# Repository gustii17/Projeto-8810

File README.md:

# Projeto 8810
`Projeto 8810 - Módulo Didático de Eletrônica Digital`

<h1 align="center">
  
</h1>

## Sumário 📋
 - [Objetivo](#objective)
 - [Motivação](#motivation)
 - [Projeto](#project)
 - [Arquivos](#files)
 - [Licença](#license)

## Objetivo 🎯
Desenvolver um módulo didático próprio e de baixo custo, capaz de reproduzir as principais funcionalidades do Datapool 8810, incluindo chaves, indicadores LED, protoboard, gerador de clock, ponta de prova e fontes de alimentação.

## Motivação 🚀
A disciplina de Eletrônica Digital é um componente fundamental na formação dos estudantes dos cursos de Engenharia que dependam de eletrônica. As atividades práticas na UFC (Universidade Federal do Ceará) são realizadas com o auxílio do módulo didático Datapool 8810, utilizado para a aplicação dos conceitos estudados em sala de aula. Entretanto, parte desses equipamentos apresenta desgaste e falhas de funcionamento, dificultando a realização dos experimentos. Além disso, os custos de manutenção ou substituição são elevados, evidenciando a necessidade de uma alternativa de baixo custo e de fácil manutenção.

## Projeto 🛠️
O projeto está dividido em basicamente 3 subprojetos, os quais são:
 - A PCB da Placa de Cima, resposável pela lógica e funcionamento geral do módulo, junto com o código do microcontrolador. _[Em Breve](./) mais informações_
 - A PCB da Placa de Baixo, resposável pelo fornecimento de eneriga. _[Clique Aqui](/docs/POWER-BOARD.md) para mais informações_
 - O Modelo 3D do módulo. _[Em Breve](./) mais informações_

## Arquivos 📂

```txt
.
|-- docs/       Documentação e Datasheets
|-- firmware/   Código do microcontrolador
|-- cad/        Modelo 3D
|-- schematics/ Esquemáticos, PCBs e simulações
|-- licenses/   Licenças do projeto
|-- assets/     Imagens
|-- README.md   Este Arquivo
```

## Licença 📝
O Projeto está licenciado sobre algumas licenças da seguinte forma:
 - Todos os arquivos dentro de [cad/](/cad) estão licenciadas sobre a licença [CC By 4.0](/licenses/CC-BY-4.0.txt).
 - Todos os arquivos dentro de [schematics/power-board/](/schematics/power-board) estão licenciadas sobre a licença [CERN OHL P](/licenses/CERN-OHL-P.txt).
 - Todos os arquivos dentro de [firmware/](/firmware) estão licenciados sobre a licença [...]()
 - Todos os arquivos dentro de [schematics/logic-board/](/schematics/logic-board) estão licenciadas sobre a licença [...]()
 - Todos os demais arquivos estão sobre a licença [CC0](/licenses/CC0.txt).

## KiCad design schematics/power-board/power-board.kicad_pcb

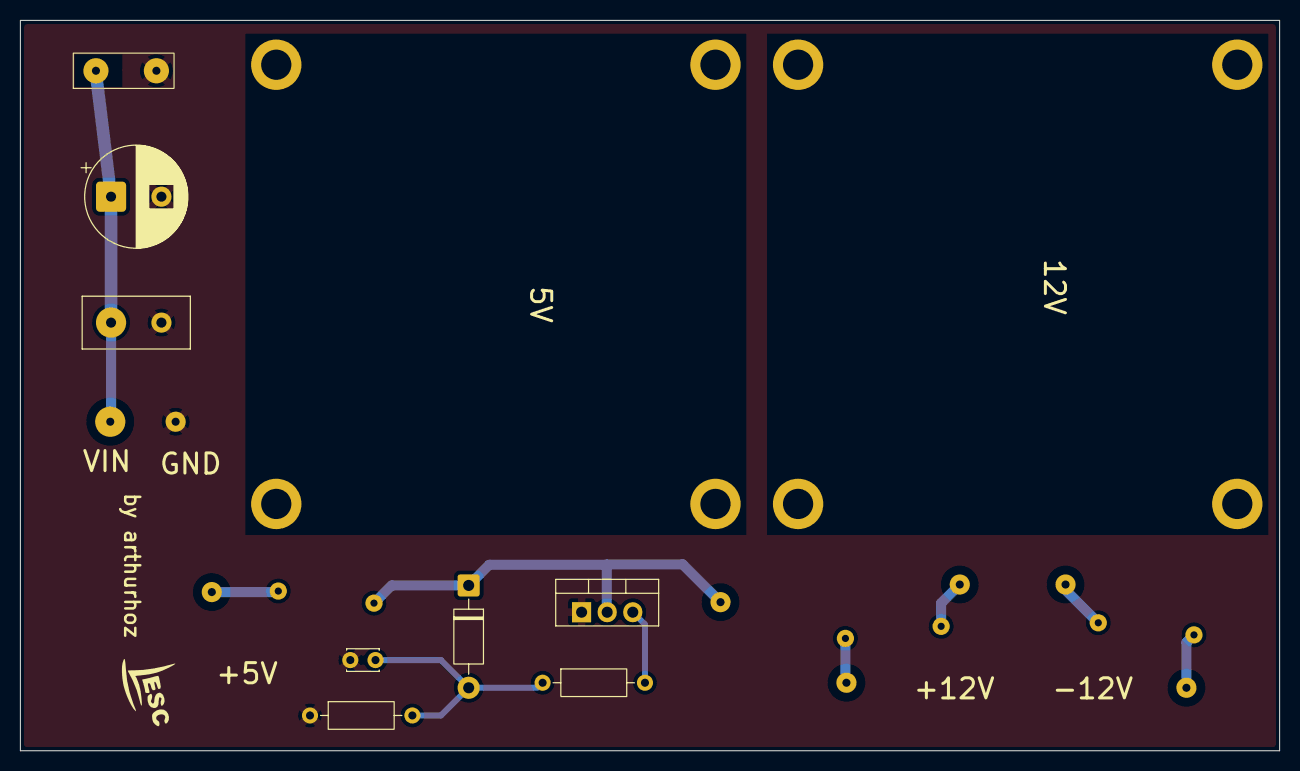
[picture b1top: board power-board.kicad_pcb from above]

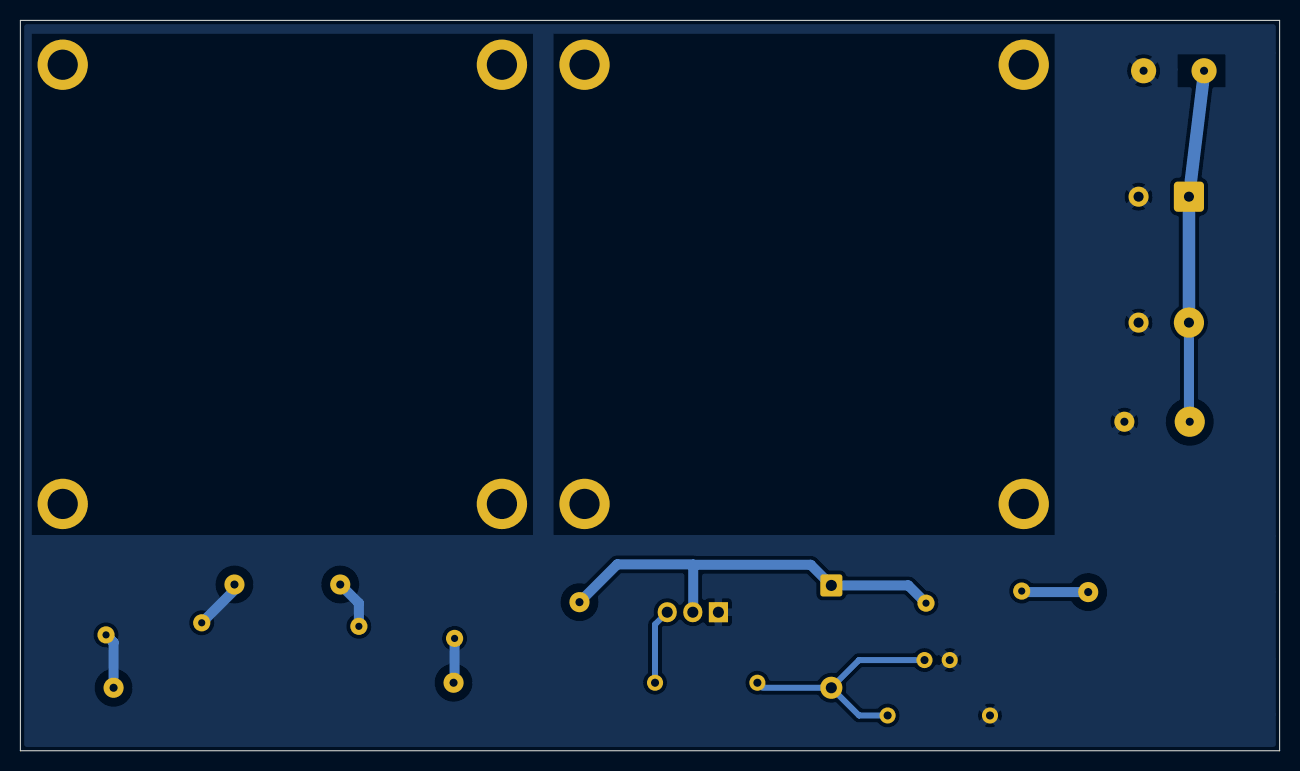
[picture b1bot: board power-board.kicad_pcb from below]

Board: 2 copper layers, 125.0 x 72.5 mm, 21 parts (2 on the bottom side), 8 nets.

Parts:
C1: 680uF; CP_Radial_D10.0mm_P5.00mm
C2: 100nF; C_Disc_D10.5mm_W5.0mm_P5.00mm
C4: 1nF; C_Disc_D3.0mm_W2.0mm_P2.50mm
D1: 1N4734A; D_DO-41_SOD81_P10.16mm_Horizontal
F1, F1#2, F1#3: Fuse; Fuse_Bourns_MF-RHT200
J1, J2: 5V; Connector
J3, J4: +12V; Connector
J5, J6: -12V; Connector
J7: GND; ConnectorGND
J8: Conn_01x01_Socket; Connector
Q1: BT151-500R; TO-220-3_Vertical
R1: 4k7 1/8W; R_Axial_DIN0207_L6.3mm_D2.5mm_P10.16mm_Horizontal
R2: 330 1/4W; R_Axial_DIN0207_L6.3mm_D2.5mm_P10.16mm_Horizontal
U1: USBC Module; USBC_Module
U2: TPS5430 Module 5V; TPS5430_Module
U3: TPS5430 Module 12V; TPS5430_Module

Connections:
/5V: D1.1 (K), F1.2, J2.1 (Pin_1_1), Q1.2 (G)
/+12V: F1#3.1, F1#3.2, J3.1 (Pin_1_1), J4.1 (Pin_1_1)
/-12V: F1#2.1, F1#2.2, J5.1 (Pin_1_1), J6.1 (Pin_1_1)
/VIN: C1.1, C2.1, J8.1 (Pin_1_1)
GND: C1.2, C2.2, C4.2, J7.1 (Pin_1_1), Q1.1 (A), R1.1, U1.0 (GND)
unnamed: C4.1, D1.2 (A), R1.2, R2.1
unnamed: F1.1, J1.1 (Pin_1_1)
unnamed: Q1.3 (K), R2.2

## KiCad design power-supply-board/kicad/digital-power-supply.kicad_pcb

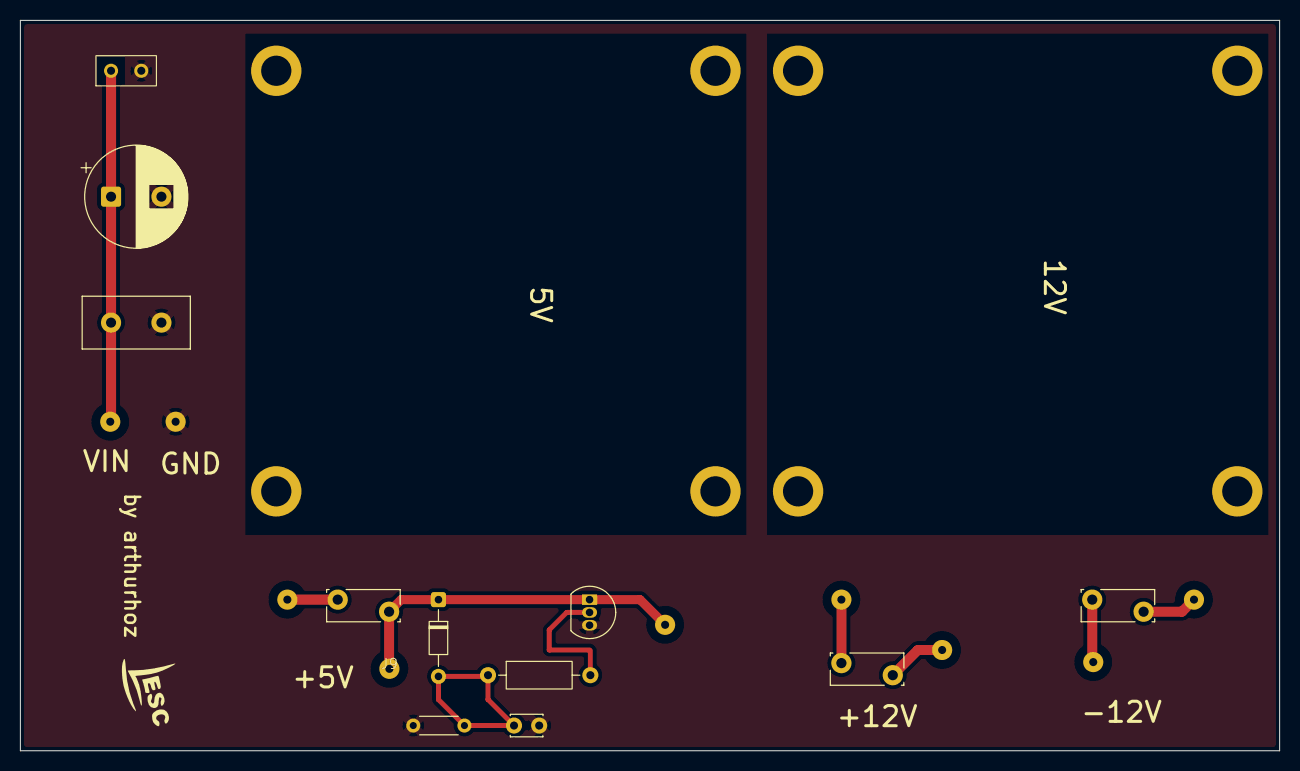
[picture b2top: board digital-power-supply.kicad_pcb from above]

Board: 2 copper layers, 125.0 x 72.5 mm, 22 parts (1 on the bottom side), 10 nets.

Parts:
C1: 680uF; CP_Radial_D10.0mm_P5.00mm
C2: 100nF; C_Disc_D10.5mm_W5.0mm_P5.00mm
C4: 1nF; C_Disc_D3.0mm_W2.0mm_P2.50mm
D1: 1N4734A; D_DO-34_SOD68_P7.62mm_Horizontal
F1: RXEF200 2A; Fuse_Bourns_MF-RG300
F2, F3: RXEF110 1A1; Fuse_Bourns_MF-RG300
J1, J2, J9: 5V; Connector
J3, J4: +12V; Connector
J5, J6: -12V; Connector
J7: GND; ConnectorGND
J8: Conn_01x01_Socket; Connector
Q1: BT151-500R; TO-92_Inline
R1: 4k7 1/8W; R_Axial_DIN0204_L3.6mm_D1.6mm_P5.08mm_Horizontal
R2: 330 1/4W; R_Axial_DIN0207_L6.3mm_D2.5mm_P10.16mm_Horizontal
U1: USBC Module; USBC_Module
U2: TPS5430 Module 5V; TPS5430_Module
U3: TPS5430 Module 12V; TPS5430_Module

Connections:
/5V: D1.1 (K), F1.2, J2.1 (Pin_1_1), J9.1 (Pin_1_1), Q1.1 (A)
/+12V: F2.2, J4.1 (Pin_1_1)
/-12V: F3.2, J6.1 (Pin_1_1)
/VIN: C1.1, C2.1, J8.1 (Pin_1_1)
GND: C1.2, C2.2, C4.2, J7.1 (Pin_1_1), Q1.3 (K), R1.1, U1.0 (GND)
unnamed: C4.1, D1.2 (A), R1.2, R2.1
unnamed: F1.1, J1.1 (Pin_1_1)
unnamed: F2.1, J3.1 (Pin_1_1)
unnamed: F3.1, J5.1 (Pin_1_1)
unnamed: Q1.2 (G), R2.2

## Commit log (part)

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2026-03-31 inicio
2026-05-17 simulacoes completas
2026-05-20 upload CH224K PD IC
2026-05-26 feat: add power supply board schematic
2026-06-02 docs: testes do módulo de energia
2026-06-16 adicionando os códigos do arduino
2026-06-17 feat: new schematic with modules and pcb creation
2026-06-24 skematico parte cima
